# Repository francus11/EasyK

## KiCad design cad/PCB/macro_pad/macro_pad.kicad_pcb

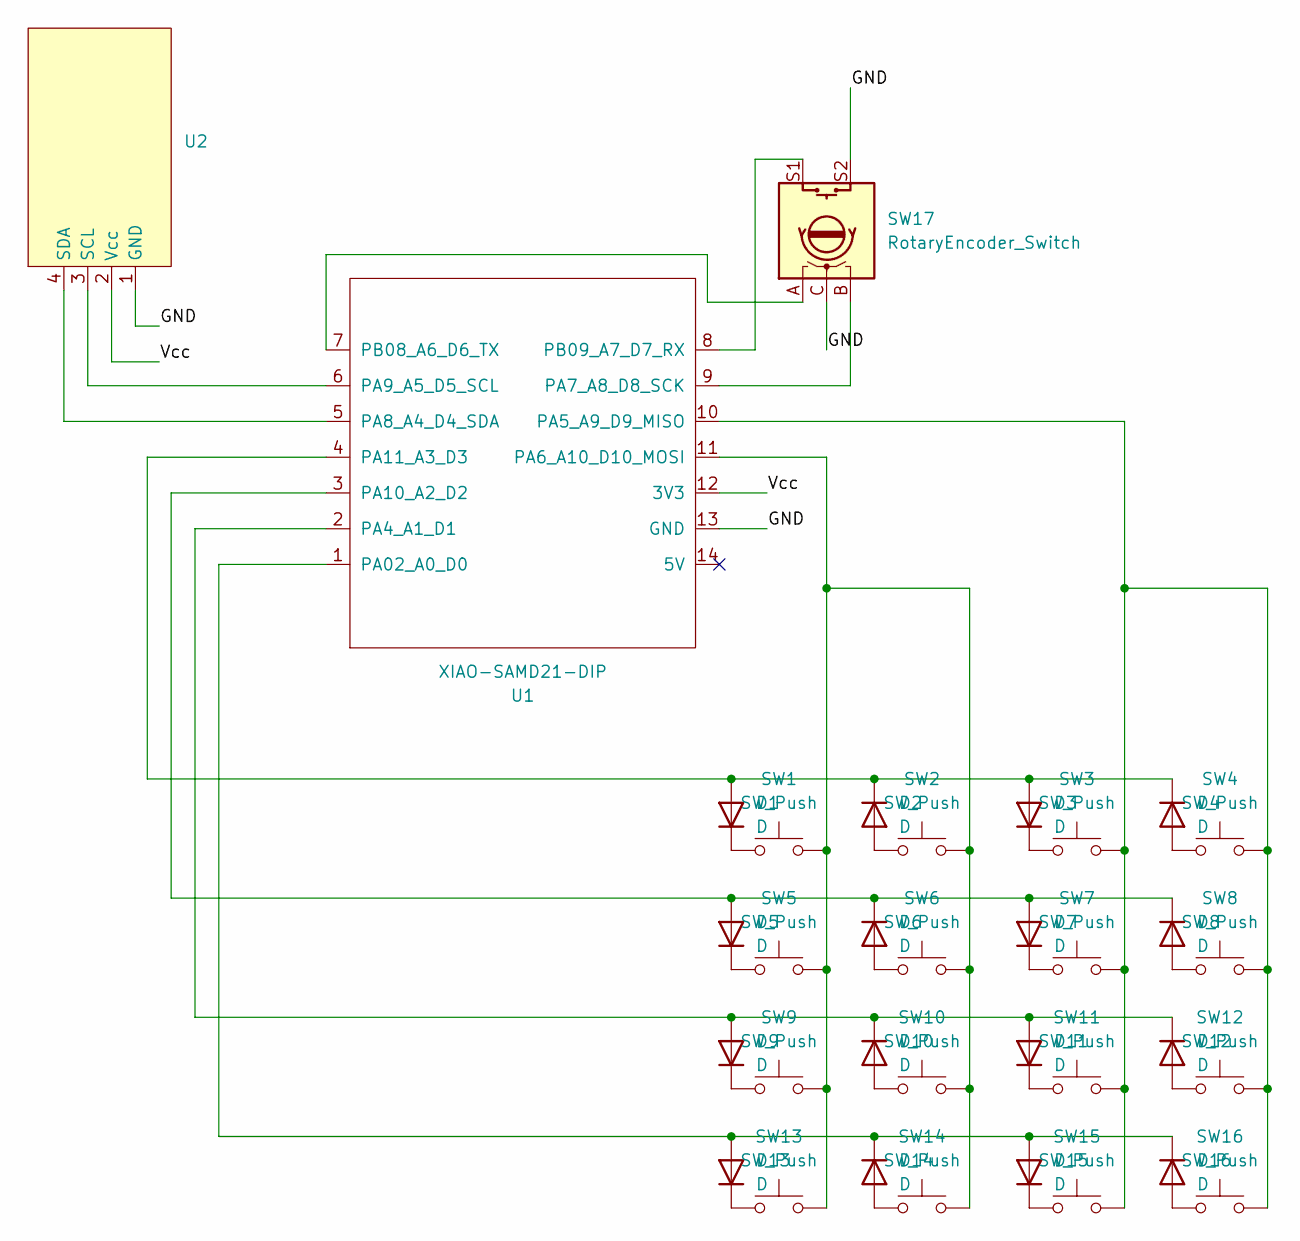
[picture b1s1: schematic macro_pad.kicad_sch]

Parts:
D1, D2, D3, D4, D5, D6, D7, D8, D9, D10, D11, D12, D13, D14, D15, D16: D; D_DO-35_SOD27_P7.62mm_Horizontal
SW1, SW2, SW3, SW4, SW5, SW6, SW7, SW8, SW9, SW10, SW11, SW12, SW13, SW14, SW15, SW16: SW_Push; SW_Cherry_MX_PCB
SW17: RotaryEncoder_Switch; RotaryEncoder_Alps_EC11E-Switch_Vertical_H20mm
U1: XIAO-SAMD21-DIP
U2: SSD1306-0.91-OLED-4pin-128x32

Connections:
/GND: SW17.C, SW17.S2, U1.13 (GND), U2.1 (GND)
/Vcc: U1.12 (3V3), U2.2 (Vcc)
unnamed: D1.2 (A), D2.1 (K), D3.2 (A), D4.1 (K), U1.4 (PA11_A3_D3)
unnamed: D1.1 (K), SW1.1
unnamed: D2.2 (A), SW2.1
unnamed: D3.1 (K), SW3.1
unnamed: D4.2 (A), SW4.1
unnamed: D5.2 (A), D6.1 (K), D7.2 (A), D8.1 (K), U1.3 (PA10_A2_D2)
unnamed: D5.1 (K), SW5.1
unnamed: D6.2 (A), SW6.1
unnamed: D7.1 (K), SW7.1
unnamed: D8.2 (A), SW8.1
unnamed: D9.1 (K), SW9.1
unnamed: D10.2 (A), SW10.1
unnamed: D9.2 (A), D10.1 (K), D11.2 (A), D12.1 (K), U1.2 (PA4_A1_D1)
unnamed: D11.1 (K), SW11.1
unnamed: D12.2 (A), SW12.1
unnamed: D13.2 (A), D14.1 (K), D15.2 (A), D16.1 (K), U1.1 (PA02_A0_D0)
unnamed: D13.1 (K), SW13.1
unnamed: D14.2 (A), SW14.1
unnamed: D15.1 (K), SW15.1
unnamed: D16.2 (A), SW16.1
unnamed: SW3.2, SW4.2, SW7.2, SW8.2, SW11.2, SW12.2, SW15.2, SW16.2, U1.10 (PA5_A9_D9_MISO)
unnamed: SW1.2, SW2.2, SW5.2, SW6.2, SW9.2, SW10.2, SW13.2, SW14.2, U1.11 (PA6_A10_D10_MOSI)
unnamed: SW17.B, U1.9 (PA7_A8_D8_SCK)
unnamed: U1.5 (PA8_A4_D4_SDA), U2.4 (SDA)
unnamed: U1.6 (PA9_A5_D5_SCL), U2.3 (SCL)
unnamed: SW17.A, U1.7 (PB08_A6_D6_TX)
unnamed: SW17.S1, U1.8 (PB09_A7_D7_RX)

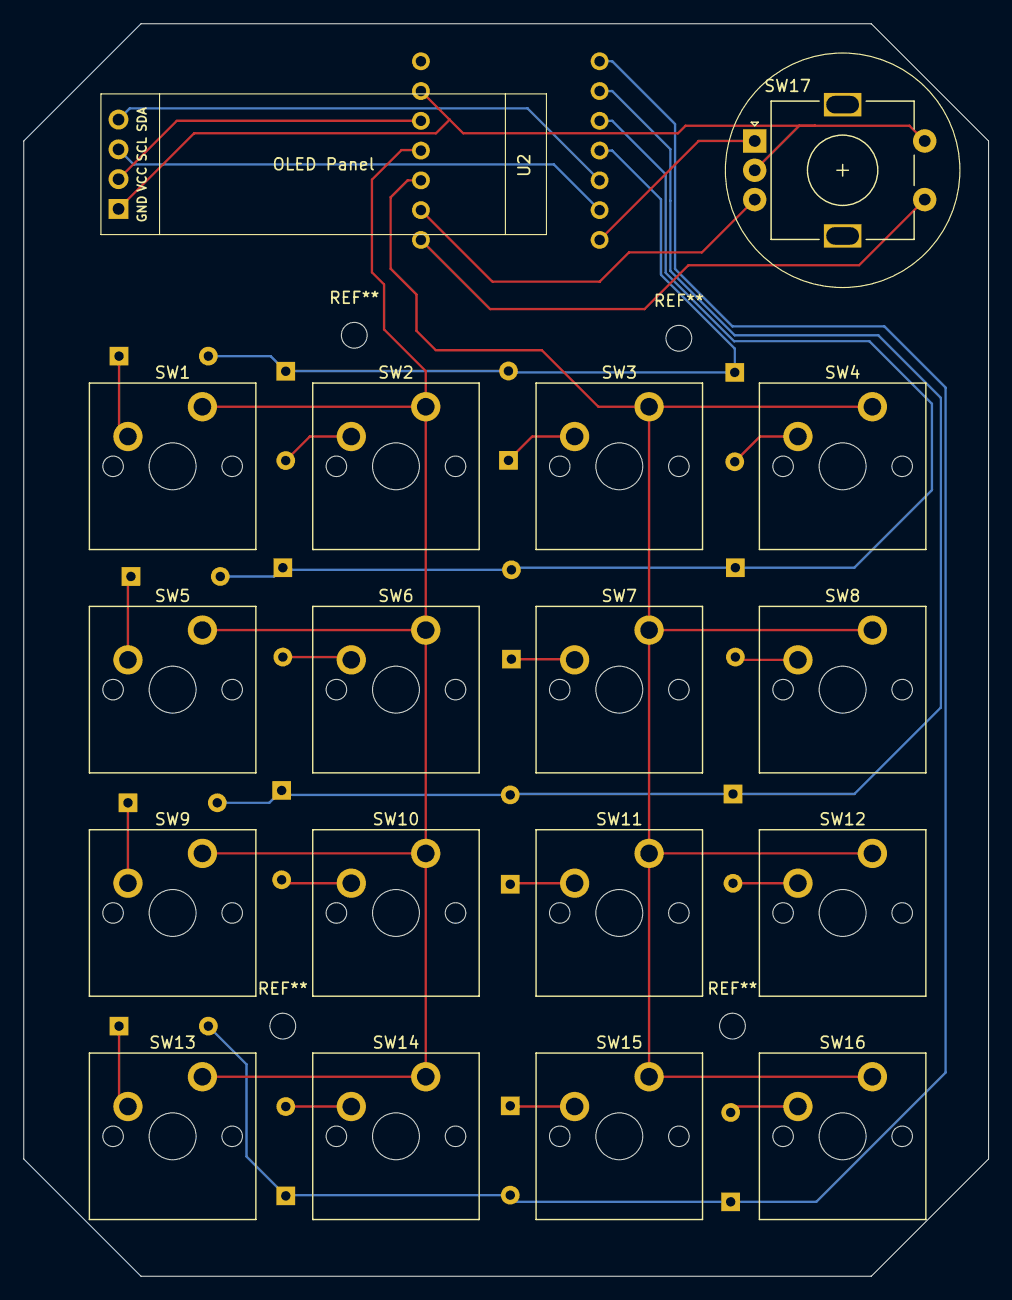
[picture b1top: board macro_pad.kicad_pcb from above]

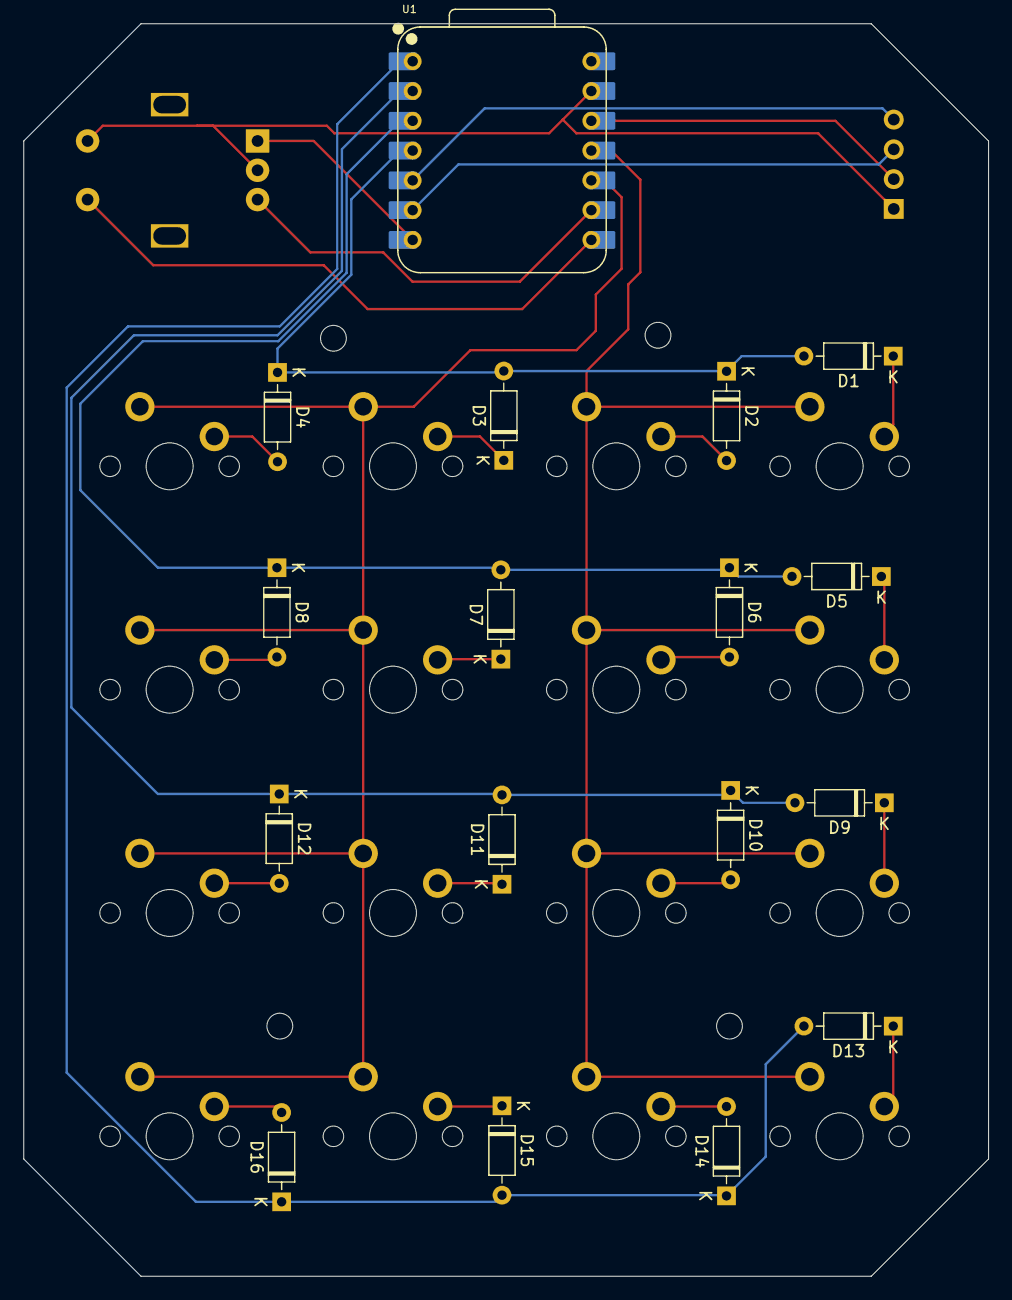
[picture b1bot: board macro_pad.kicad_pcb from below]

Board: 2 copper layers, 82.3 x 106.8 mm, 35 parts (17 on the bottom side), 29 nets.

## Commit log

2024-12-17 created simple pcb schematic
2024-12-18 edited component placing added 3d models
2024-12-18 small fix
2024-12-18 moved encoder and mcu
2024-12-23 modified shape of pcb
2024-12-23 added 3d model of device and enclosure
2024-12-24 created general HID device class
2024-12-27 created simple keyboard implementation
2024-12-28 Created small framework for handling physical inputs and actions
2024-12-29 added support for different types of actions (press, release, click)
2024-12-29 changed Action action variable to pointer
2024-12-29 added deserialization
2024-12-29 changed actions to pointers
2024-12-29 refactored from Arduino String to std::string
2024-12-30 created empty action for buttons without assigned action
2024-12-30 swapped json library to ArduinoJson
2024-12-30 swapped library to ArduinoJson
2024-12-30 swap library
2024-12-30 repo settings
2025-01-03 Added getPressedState method added new way of determining which input state should be concidered as pressed
2025-01-03 created wrapper for Button classs
2025-01-03 switched heritage to public
2025-01-07 createt application project
2025-01-07 Added window for capturing keys combinations added placeholder button in main window
2025-01-08 Added style to buttons
2025-01-11 Created KeyButton element Created key press logic
2025-01-12 Created ActionStackPanelItem, which is graphic representation of action assigned to button added icons implemented "add action" mechanism sketch
2025-01-12 Removed useless comments
2025-01-12 refactor
2025-01-12 extended interface and classes
2025-01-12 hotfix
2025-01-13 changed name from Macro to MacroAction
2025-01-13 added simple window to capture key combinations
2025-01-13 changed type of property (refactor)
2025-01-13 changed name of class
2025-01-14 (fix) changed label string . Now it doesn't contain plus sign if it's single key combination
2025-01-14 added KeyboardAction class added ClickType enum KeysCapture returns object of class KeyboardAction
2025-01-14 deleted commented code
2025-01-14 Created DelayAction
2025-01-14 changed accesibility
2025-01-17 Created classes that represent inputs on a keyboard and interface for them
2025-01-17 Created serialization classes
2025-01-17 Added dependency System.IO.Ports
2025-01-17 Added MacroAction class
2025-01-17 implemented clearReport methods
2025-01-18 Added serialization to firmware
2025-01-18 added example of end program
2025-01-18 added serialization for Encoder
2025-01-18 fixed issue with backslashes
2025-01-18 modified serialization added private field state added enum KeyState
2025-01-18 added serialization added deserialization
2025-01-18 removed unnecesary serial logs
2025-01-19 Changed type numbers added none type
2025-01-19 Added new icon
2025-01-20 upgraded toolbar
2025-01-20 added pre-compile file to include json file
2025-01-20 main file for tests
2025-01-22 Improved toolbar
2025-01-22 Added deserialization Small fixes
2025-01-22 Added method to convert UsageId to Key
2025-01-22 Added events for delete and edit
2025-01-22 Created new action
2025-01-22 Added DelayAction
2025-01-22 Modified EmptyAction
2025-01-23 Added serialization and deserialization
2025-01-23 Implemented saving ant initializing
2025-01-23 Working app(kinda)
